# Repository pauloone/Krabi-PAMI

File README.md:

# Krabi PAMIs

## board
electronics schematics & PCB designs

###
Elements:
- an STM32L0
- an 3.3V power supply
- a full H Drive driver for 2 motors (1A max)
- 4 LEDS outputs connected 2 the 2 motors PWM
- A switch connector
- 2 connectors for VL53L1X ToF sensors
- 2 connectors for CNY70 for line following
- A power connector with 9V for electronics & power and 3V to raise voltage up to 12V for motors, as well as AU connecting ground
- A STM32 debug connector
- A start connector that will inhibit H drives & CNY70 emitters when grounded. Pulled up to 3.3V

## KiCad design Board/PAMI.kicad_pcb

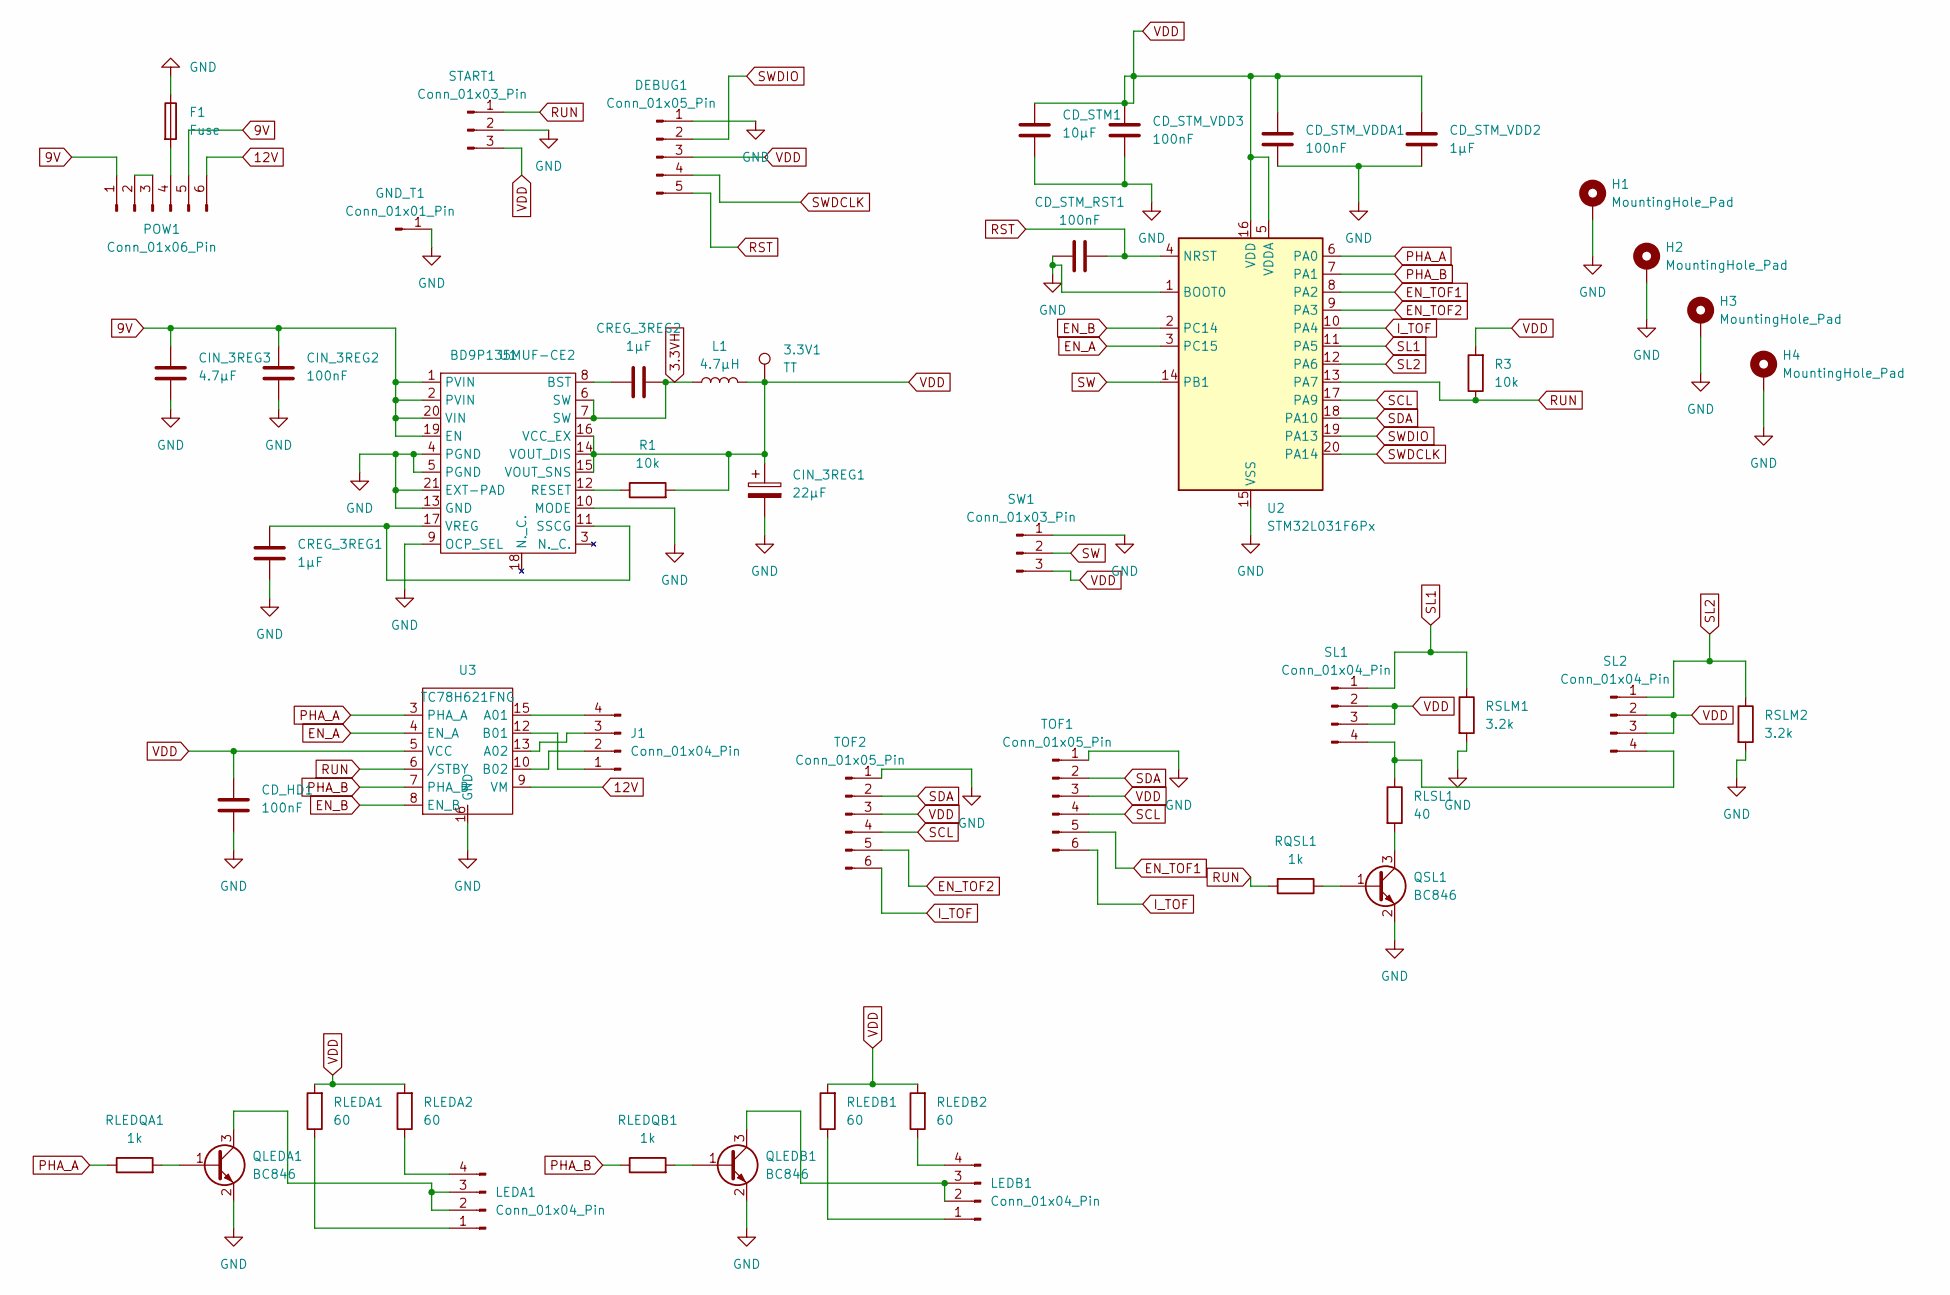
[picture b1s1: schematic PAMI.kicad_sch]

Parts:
3.3V1: TT; TestPoint_Pad_D1.0mm
CD_HD1: 100nF; C_0603_1608Metric
CD_STM1: 10µF; C_0805_2012Metric
CD_STM_RST1: 100nF; C_0603_1608Metric
CD_STM_VDD2: 1µF; C_0603_1608Metric
CD_STM_VDD3: 100nF; C_0603_1608Metric
CD_STM_VDDA1: 100nF; C_0603_1608Metric
CIN_3REG1: 22µF; CP_EIA-3528-21_Kemet-B
CIN_3REG2: 100nF; C_0603_1608Metric
CIN_3REG3: 4.7µF; C_0805_2012Metric
CREG_3REG1, CREG_3REG2: 1µF; C_0603_1608Metric
DEBUG1: Conn_01x05_Pin; PinHeader_1x05_P1.00mm_Vertical
F1: Fuse; Fuse_1206_3216Metric
GND_T1: Conn_01x01_Pin; Pin_D0.7mm_L6.5mm_W1.8mm_FlatFork
H1, H2, H3, H4: MountingHole_Pad; MountingHole_2.2mm_M2_Pad
J1: Conn_01x04_Pin; SolderWire-0.5sqmm_1x04_P4.6mm_D0.9mm_OD2.1mm
L1: 4.7µH; L_1008_2520Metric
LEDA1: Conn_01x04_Pin; PinHeader_1x04_P1.00mm_Vertical
LEDB1: Conn_01x04_Pin; PinHeader_1x04_P1.00mm_Vertical
POW1: Conn_01x06_Pin; SolderWire-0.5sqmm_1x06_P4.6mm_D0.9mm_OD2.1mm
QLEDA1: BC846; SOT-23
QLEDB1: BC846; SOT-23
QSL1: BC846; SOT-23
R1, R3: 10k; R_0603_1608Metric
RLEDA1, RLEDA2: 60; R_0603_1608Metric
RLEDB1, RLEDB2: 60; R_0603_1608Metric
RLEDQA1: 1k; R_0603_1608Metric
RLEDQB1: 1k; R_0603_1608Metric
RLSL1: 40; R_0603_1608Metric
RQSL1: 1k; R_0603_1608Metric
RSLM1, RSLM2: 3.2k; R_0603_1608Metric
SL1, SL2: Conn_01x04_Pin; PinHeader_1x04_P1.00mm_Vertical
START1: Conn_01x03_Pin; PinHeader_1x03_P1.00mm_Vertical
SW1: Conn_01x03_Pin; PinHeader_1x03_P1.00mm_Vertical
TOF1, TOF2: Conn_01x05_Pin; PinHeader_1x06_P1.00mm_Vertical
U1: BD9P135MUF-CE2; VQFN20FV4040
U2: STM32L031F6Px; TSSOP-20_4.4x6.5mm_P0.65mm
U3: TC78H621FNG; TSSOP-16_4.4x5mm_P0.65mm

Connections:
3.3VH: CREG_3REG2.2, L1.1, U1.6 (SW), U1.7 (SW)
9V: CIN_3REG2.1, CIN_3REG3.1, POW1.1, POW1.5, U1.1 (PVIN), U1.2 (PVIN), U1.19 (EN), U1.20 (VIN)
12V: POW1.6, U3.9 (VM)
EN_A: U2.3 (PC15), U3.4 (EN_A)
EN_B: U2.2 (PC14), U3.8 (EN_B)
EN_TOF1: TOF1.5, U2.8 (PA2)
EN_TOF2: TOF2.5, U2.9 (PA3)
GND: CD_HD1.2, CD_STM1.2, CD_STM_RST1.2, CD_STM_VDD2.1, CD_STM_VDD3.1, CD_STM_VDDA1.1, CIN_3REG1.2, CIN_3REG2.2, CIN_3REG3.2, CREG_3REG1.2, DEBUG1.1, F1.1, GND_T1.1, H1.1, H2.1, H3.1, H4.1, QLEDA1.2 (E), QLEDB1.2 (E), QSL1.2 (E), RSLM1.2, RSLM2.2, START1.2, SW1.1, TOF1.1, TOF2.1, U1.4 (PGND), U1.5 (PGND), U1.9 (OCP_SEL), U1.10 (MODE), U1.13 (GND), U1.21 (EXT-PAD), U2.1 (BOOT0), U2.15 (VSS), U3.11 (GND), U3.14 (GND), U3.16 (GND)
I_TOF: TOF1.6, TOF2.6, U2.10 (PA4)
unnamed: J1.1, U3.12 (B01)
unnamed: J1.2, U3.10 (B02)
unnamed: J1.3, U3.13 (A02)
unnamed: J1.4, U3.15 (A01)
unnamed: LEDA1.1, RLEDA1.1
unnamed: LEDA1.2, LEDA1.3, QLEDA1.3 (C)
unnamed: LEDA1.4, RLEDA2.1
unnamed: LEDB1.1, RLEDB1.1
unnamed: LEDB1.2, LEDB1.3, QLEDB1.3 (C)
unnamed: LEDB1.4, RLEDB2.1
unnamed: POW1.2, POW1.3
unnamed: F1.2, POW1.4
unnamed: QLEDA1.1 (B), RLEDQA1.2
unnamed: QLEDB1.1 (B), RLEDQB1.2
unnamed: QSL1.1 (B), RQSL1.1
unnamed: QSL1.3 (C), RLSL1.2
unnamed: RLSL1.1, SL1.4, SL2.4
unnamed: CREG_3REG2.1, U1.8 (BST)
unnamed: R1.1, U1.12 (RESET)
unnamed: CREG_3REG1.1, U1.11 (SSCG), U1.17 (VREG)
PHA_A: RLEDQA1.1, U2.6 (PA0), U3.3 (PHA_A)
PHA_B: RLEDQB1.1, U2.7 (PA1), U3.7 (PHA_B)
RST: CD_STM_RST1.1, DEBUG1.5, U2.4 (NRST)
RUN: R3.1, RQSL1.2, START1.1, U2.13 (PA7), U3.6 (/STBY)
SCL: TOF1.4, TOF2.4, U2.17 (PA9)
SDA: TOF1.2, TOF2.2, U2.18 (PA10)
SL1: RSLM1.1, SL1.1, U2.11 (PA5)
SL2: RSLM2.1, SL2.1, U2.12 (PA6)
SW: SW1.2, U2.14 (PB1)
SWDCLK: DEBUG1.4, U2.20 (PA14)
SWDIO: DEBUG1.2, U2.19 (PA13)
VDD: 3.3V1.1, CD_HD1.1, CD_STM1.1, CD_STM_VDD2.2, CD_STM_VDD3.2, CD_STM_VDDA1.2, CIN_3REG1.1, DEBUG1.3, L1.2, R1.2, R3.2, RLEDA1.2, RLEDA2.2, RLEDB1.2, RLEDB2.2, SL1.2, SL1.3, SL2.2, SL2.3, START1.3, SW1.3, TOF1.3, TOF2.3, U1.14 (VOUT_DIS), U1.15 (VOUT_SNS), U1.16 (VCC_EX), U2.5 (VDDA), U2.16 (VDD), U3.5 (VCC)

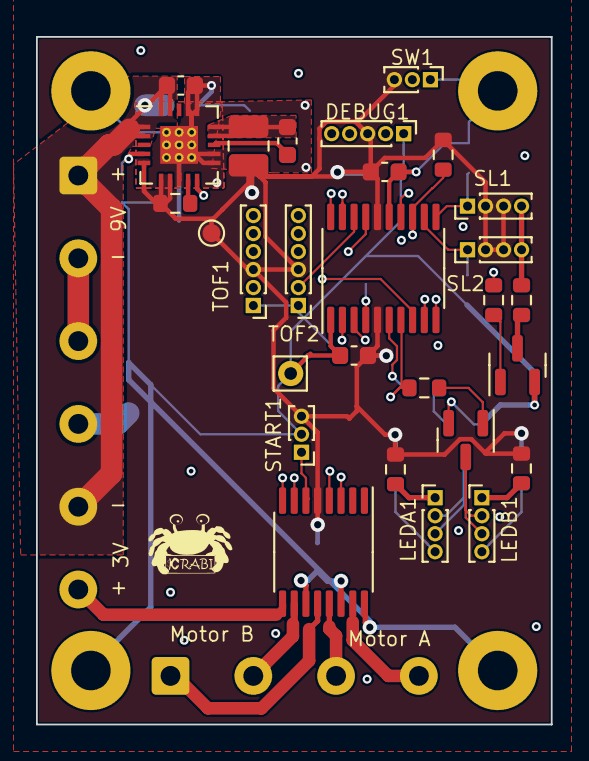
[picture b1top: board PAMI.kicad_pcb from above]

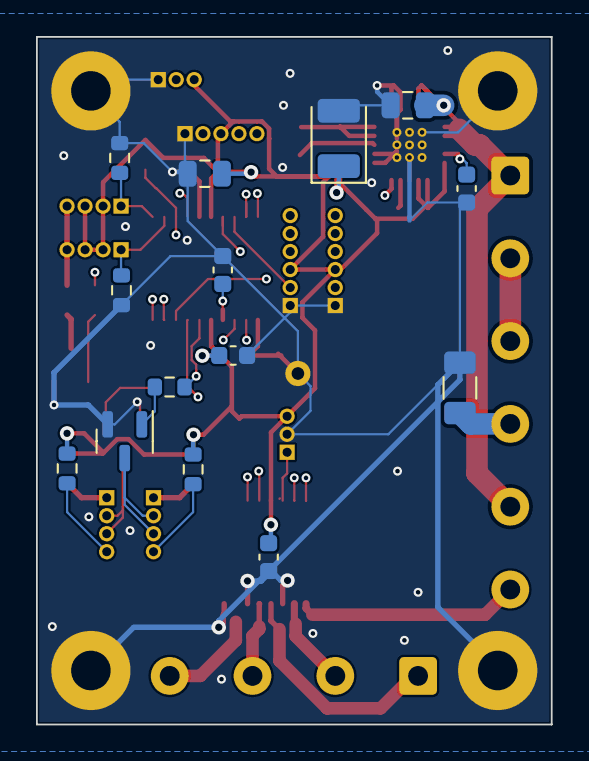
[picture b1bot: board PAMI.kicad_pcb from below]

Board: 4 copper layers, 28.6 x 38.2 mm, 48 parts (14 on the bottom side), 41 nets.

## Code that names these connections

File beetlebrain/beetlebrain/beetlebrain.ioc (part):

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Mcu.Name=STM32L031F(4-6)Px
Mcu.Package=TSSOP20
Mcu.UserName=STM32L031F6Px
PA0-CK_IN.GPIOParameters=GPIO_Label
PA0-CK_IN.GPIO_Label=PHA_A
PA0-CK_IN.Signal=S_TIM2_CH1
PA1.GPIOParameters=GPIO_Label
PA1.GPIO_Label=PHA_B
PA1.Signal=S_TIM2_CH2
PA10.Mode=I2C
PA10.Signal=I2C1_SDA
PA13.Mode=Serial_Wire
PA13.Signal=SYS_SWDIO
PA14.Mode=Serial_Wire
PA14.Signal=SYS_SWCLK
PA2.GPIOParameters=GPIO_PuPd,GPIO_Label
PA2.GPIO_Label=EN_TOF1
PA2.GPIO_PuPd=GPIO_PULLDOWN
PA2.Signal=GPIO_Output
PA3.GPIOParameters=GPIO_PuPd,GPIO_Label
PA3.GPIO_Label=EN_TOF2
PA3.GPIO_PuPd=GPIO_PULLDOWN
PA3.Signal=GPIO_Output
PA4.GPIOParameters=GPIO_PuPd,GPIO_Label
PA4.GPIO_Label=I_OTF
PA4.GPIO_PuPd=GPIO_PULLUP
PA4.Signal=GPIO_Input
PA5.Mode=IN5
PA5.Signal=ADC_IN5
PA6.Mode=IN6
PA6.Signal=ADC_IN6
PA7.GPIOParameters=GPIO_PuPd,GPIO_Label,GPIO_ModeDefaultEXTI
PA7.GPIO_Label=RUN
PA7.GPIO_ModeDefaultEXTI=GPIO_MODE_IT_RISING_FALLING
PA7.GPIO_PuPd=GPIO_PULLUP
PA7.Signal=GPXTI7
PA9.Mode=I2C
PA9.Signal=I2C1_SCL
PB1.GPIOParameters=GPIO_PuPd,GPIO_Label
PB1.GPIO_Label=SWITCH
PB1.GPIO_PuPd=GPIO_PULLUP
PB1.Signal=GPIO_Input
PC14-OSC32_IN.Signal=GPIO_Output
PC15-OSC32_OUT.GPIOParameters=GPIO_PuPd
PC15-OSC32_OUT.GPIO_PuPd=GPIO_PULLDOWN
PC15-OSC32_OUT.Signal=GPIO_Output
RCC.HSE_VALUE=8000000
RCC.SYSCLKFreq_VALUE=2097000
board=custom

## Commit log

2023-10-08 Add schematics & PCB design
2023-10-08 Fix some minor glith on plan & add logo
2023-10-10 Fix DCR
2023-11-02 review (fix warnings + GND copper fill on internal layers)
2024-04-02 Board update
2024-04-02 Generate beetlebrain basic code
2024-04-02 Configure RUN pin interrupt
2024-04-02 Register interrupt callback and enable interrupt
2024-04-02 RUN interrupt configured and tested with software trigger
2024-04-02 Calibrate ADC
2024-04-11 Simple PID
2024-05-03 Update WE before coupe
2024-05-05 Working PWM
2024-05-07 Last push before the competition
